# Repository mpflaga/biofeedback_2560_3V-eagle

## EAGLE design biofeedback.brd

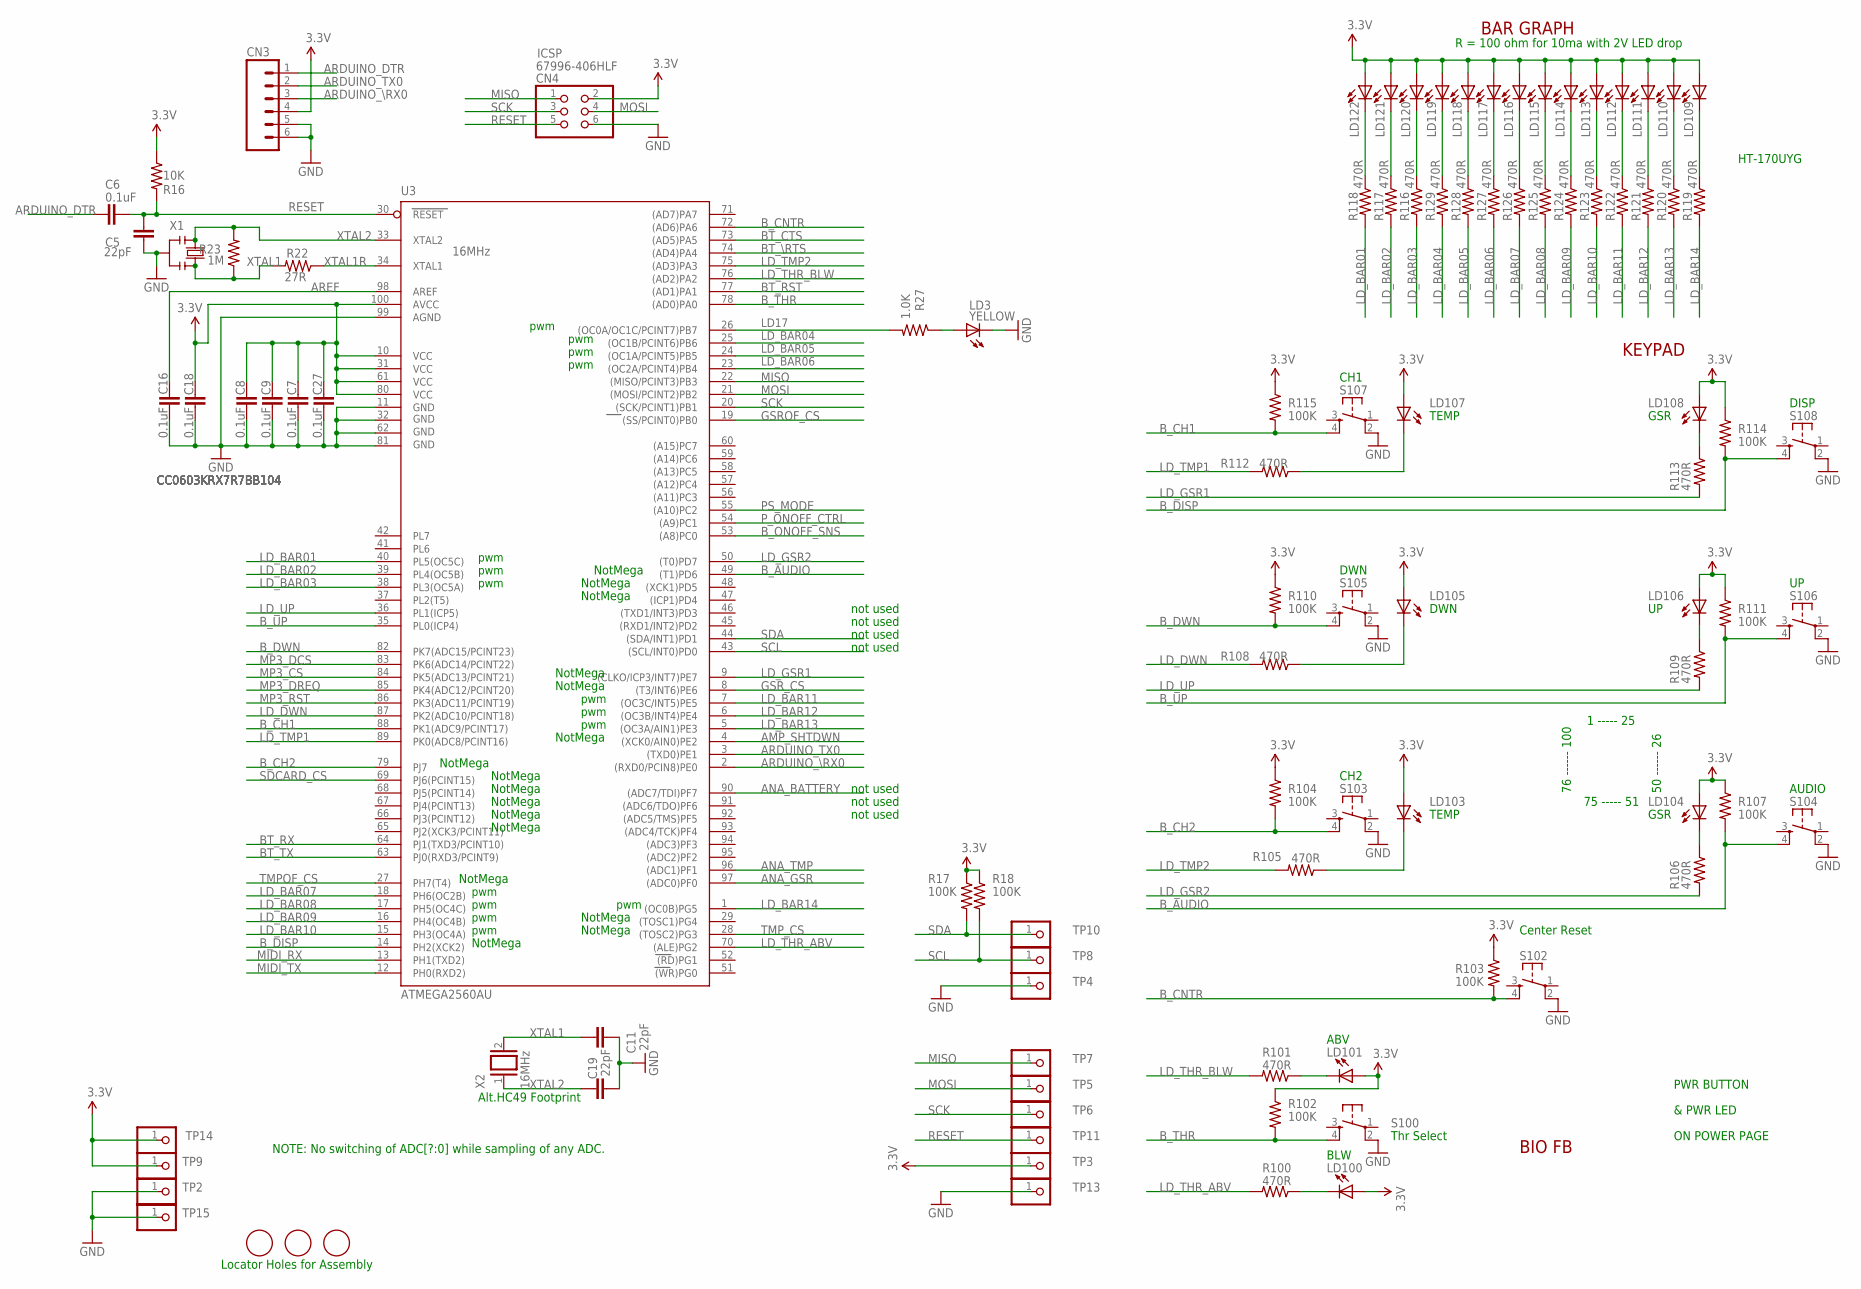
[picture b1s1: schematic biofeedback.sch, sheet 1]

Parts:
C5, C11, C19: 22pF; C0603; PARTNO GRM0335C1E220JD01D
C6, C7, C8, C9, C16, C18, C27: 0.1uF; C0603; PARTNO CC0603KRX7R7BB104
CN3: NSTUFF; 1X06; PARTNO 640456-6
CN4: ICSP; 2X03; PARTNO 67996-406HLF
LD3: YELLOW; CHIP-LED0805; PARTNO APT2012YC
LD100, LD101, LD103, LD104, LD105, LD106, LD107, LD108, LD109, LD110, LD111, LD112, LD113, LD114, LD115, LD116, LD117, LD118, LD119, LD120, LD121, LD122: GREEN; CHIP-LED0805; PARTNO LG R971-KN-1-0-20-R18
MN1, MN2, MN3: FIDUCIALMOUNT; FIDUCIA-MOUNT
R16: 10K; R0603; PARTNO RC0603JR-0710KL
R17, R18, R102, R103, R104, R107, R110, R111, R114, R115: 100K; R0603; PARTNO RC0603JR-07100KL
R22: 27R; R0603; PARTNO ERJ-3EKF27R0V
R23: 1M; R0603; PARTNO RC0603JR-071ML
R27: 1.0K; R0603; PARTNO RC0603JR-071KL
R100, R101, R105, R106, R108, R109, R112, R113, R116, R117, R118, R119, R120, R121, R122, R123, R124, R125, R126, R127, R128, R129: 470R; R0603; PARTNO RC0603JR-07470RL
S100, S102, S103, S104, S105, S106, S107, S108: SPST-NO; TACTILE_SWITCH_SMD_6MM_SQ; PARTNO TL3301PF160QG
TP2, TP3, TP4, TP5, TP6, TP7, TP8, TP9, TP10, TP11, TP13, TP14, TP15: NSTUFF; 1X01
U3: ATMEGA2560AU; TQFP100; PARTNO ATMEGA2560-16AU
X1: 16MHz; RESONATOR; PARTNO AWSCR-16.00CV-T
X2: 16MHz; QS; PARTNO ATS16B

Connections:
3.3V: C7.2, C8.2, C9.2, C18.2, C27.2, CN3.4, CN4.2, LD100.A, LD101.A, LD103.A, LD104.A, LD105.A, LD106.A, LD107.A, LD108.A, LD109.A, LD110.A, LD111.A, LD112.A, LD113.A, LD114.A, LD115.A, LD116.A, LD117.A, LD118.A, LD119.A, LD120.A, LD121.A, LD122.A, R16.1, R17.1, R18.1, R102.1, R103.1, R104.1, R107.1, R110.1, R111.1, R114.1, R115.1, TP3.1, TP9.1, TP14.1, U3.10 (VCC), U3.31 (VCC1), U3.61 (VCC2), U3.80 (VCC3), U3.100 (AVCC); also elsewhere on the board
AMP_SHTDWN: U3.4 ((XCK0/AIN0)PE2); also elsewhere on the board
ANA_BATTERY: U3.90 ((ADC7/TDI)PF7); also elsewhere on the board
ANA_GSR: U3.97 ((ADC0)PF0); also elsewhere on the board
ANA_TMP: U3.96 ((ADC1)PF1); also elsewhere on the board
ARDUINO_DTR: C6.1, CN3.1
ARDUINO_TX0: CN3.2, U3.3 ((TXD0)PE1)
ARDUINO_\RX0: CN3.3, U3.2 ((RXD0/PCIN8)PE0)
AREF: C16.2, U3.98 (AREF)
BT_CTS: U3.73 ((AD5)PA5); also elsewhere on the board
BT_RST: U3.77 ((AD1)PA1); also elsewhere on the board
BT_RX: U3.64 (PJ1(TXD3/PCINT10)); also elsewhere on the board
BT_TX: U3.63 (PJ0(RXD3/PCINT9)); also elsewhere on the board
BT_\RTS: U3.74 ((AD4)PA4); also elsewhere on the board
B_AUDIO: R107.2, S104.4, U3.49 ((T1)PD6)
B_CH1: R115.2, S107.4, U3.88 (PK1(ADC9/PCINT17))
B_CH2: R104.2, S103.4, U3.79 (PJ7)
B_CNTR: R103.2, S102.4, U3.72 ((AD6)PA6)
B_DISP: R114.2, S108.4, U3.14 (PH2(XCK2))
B_DWN: R110.2, S105.4, U3.82 (PK7(ADC15/PCINT23))
B_ONOFF_SNS: U3.53 ((A8)PC0); also elsewhere on the board
B_THR: R102.2, S100.4, U3.78 ((AD0)PA0)
B_UP: R111.2, S106.4, U3.35 (PL0(ICP4))
G2: LD107.C, R112.1
GND: C5.2, C7.1, C8.1, C9.1, C11.1, C16.1, C18.1, C19.1, C27.1, CN3.5, CN3.6, CN4.6, LD3.C, S100.2, S102.2, S103.2, S104.2, S105.2, S106.2, S107.2, S108.2, TP2.1, TP4.1, TP13.1, TP15.1, U3.11 (GND), U3.32 (GND1), U3.62 (GND2), U3.81 (GND3), U3.99 (AGND), X1.2; also elsewhere on the board
GSROF_CS: U3.19 ((SS/PCINT0)PB0); also elsewhere on the board
GSR_CS: U3.8 ((T3/INT6)PE6); also elsewhere on the board
LD17: R27.2, U3.26 ((OC0A/OC1C/PCINT7)PB7)
LD_BAR01: R118.2, U3.40 (PL5(OC5C))
LD_BAR02: R117.2, U3.39 (PL4(OC5B))
LD_BAR03: R116.2, U3.38 (PL3(OC5A))
LD_BAR04: R129.2, U3.25 ((OC1B/PCINT6)PB6)
LD_BAR05: R128.2, U3.24 ((OC1A/PCINT5)PB5)
LD_BAR06: R127.2, U3.23 ((OC2A/PCINT4)PB4)
LD_BAR07: R126.2, U3.18 (PH6(OC2B))
LD_BAR08: R125.2, U3.17 (PH5(OC4C))
LD_BAR09: R124.2, U3.16 (PH4(OC4B))
LD_BAR10: R123.2, U3.15 (PH3(OC4A))
LD_BAR11: R122.2, U3.7 ((OC3C/INT5)PE5)
LD_BAR12: R121.2, U3.6 ((OC3B/INT4)PE4)
LD_BAR13: R120.2, U3.5 ((OC3A/AIN1)PE3)
LD_BAR14: R119.2, U3.1 ((OC0B)PG5)
LD_DWN: R108.2, U3.87 (PK2(ADC10/PCINT18))
LD_GSR1: R113.2, U3.9 ((CLKO/ICP3/INT7)PE7)
LD_GSR2: R106.2, U3.50 ((T0)PD7)
LD_THR_ABV: R100.2, U3.70 ((ALE)PG2)
LD_THR_BLW: R101.2, U3.76 ((AD2)PA2)
LD_TMP1: R112.2, U3.89 (PK0(ADC8/PCINT16))
LD_TMP2: R105.2, U3.75 ((AD3)PA3)
LD_UP: R109.2, U3.36 (PL1(ICP5))
MIDI_RX: U3.13 (PH1(TXD2)); also elsewhere on the board
MIDI_TX: U3.12 (PH0(RXD2)); also elsewhere on the board
MISO: CN4.1, TP7.1, U3.22 ((MISO/PCINT3)PB3); also elsewhere on the board
MOSI: CN4.4, TP5.1, U3.21 ((MOSI/PCINT2)PB2); also elsewhere on the board
MP3_CS: U3.84 (PK5(ADC13/PCINT21)); also elsewhere on the board
MP3_DCS: U3.83 (PK6(ADC14/PCINT22)); also elsewhere on the board
MP3_DREQ: U3.85 (PK4(ADC12/PCINT20)); also elsewhere on the board
MP3_RST: U3.86 (PK3(ADC11/PCINT19)); also elsewhere on the board
unnamed: LD105.C, R108.1
unnamed: LD106.C, R109.1
unnamed: LD122.C, R118.1
unnamed: LD121.C, R117.1
unnamed: LD120.C, R116.1
unnamed: LD119.C, R129.1
unnamed: LD118.C, R128.1
unnamed: LD117.C, R127.1
unnamed: LD116.C, R126.1
unnamed: LD115.C, R125.1
unnamed: LD114.C, R124.1
unnamed: LD113.C, R123.1
unnamed: LD112.C, R122.1
unnamed: LD111.C, R121.1
unnamed: LD110.C, R120.1
unnamed: LD109.C, R119.1
unnamed: LD103.C, R105.1
unnamed: LD104.C, R106.1
unnamed: LD101.C, R101.1
unnamed: LD100.C, R100.1
unnamed: LD108.C, R113.1
unnamed: LD3.A, R27.1
PS_MODE: U3.55 ((A10)PC2); also elsewhere on the board
P_ONOFF_CTRL: U3.54 ((A9)PC1); also elsewhere on the board
RESET: C5.1, C6.2, CN4.5, R16.2, TP11.1, U3.30 (RESET)
SCK: CN4.3, TP6.1, U3.20 ((SCK/PCINT1)PB1); also elsewhere on the board
SCL: R18.2, TP8.1, U3.43 ((SCL/INT0)PD0)
SDA: R17.2, TP10.1, U3.44 ((SDA/INT1)PD1)
SDCARD_CS: U3.69 (PJ6(PCINT15)); also elsewhere on the board
TMPOF_CS: U3.27 (PH7(T4)); also elsewhere on the board
TMP_CS: U3.28 ((TOSC2)PG3); also elsewhere on the board
XTAL1: C11.2, R22.2, R23.1, X1.3, X2.2
XTAL1R: R22.1, U3.34 (XTAL1)
XTAL2: C19.2, R23.2, U3.33 (XTAL2), X1.1, X2.1

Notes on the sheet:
Alt.HC49 Footprint
BIO FB
pwm
NOTE: No switching of ADC[?:0] while sampling of any ADC.
BAR GRAPH
CH1
ABV
BLW
DISP
DWN
Thr Select
Center Reset
KEYPAD
CH2
AUDIO
TEMP
PWR BUTTON
& PWR LED
ON POWER PAGE
Locator Holes for Assembly
not used
NotMega
GSR
R = 100 ohm for 10ma with 2V LED drop
HT-170UYG
1 ----- 25
75 ----- 51
50 ------ 26
76 ------ 100

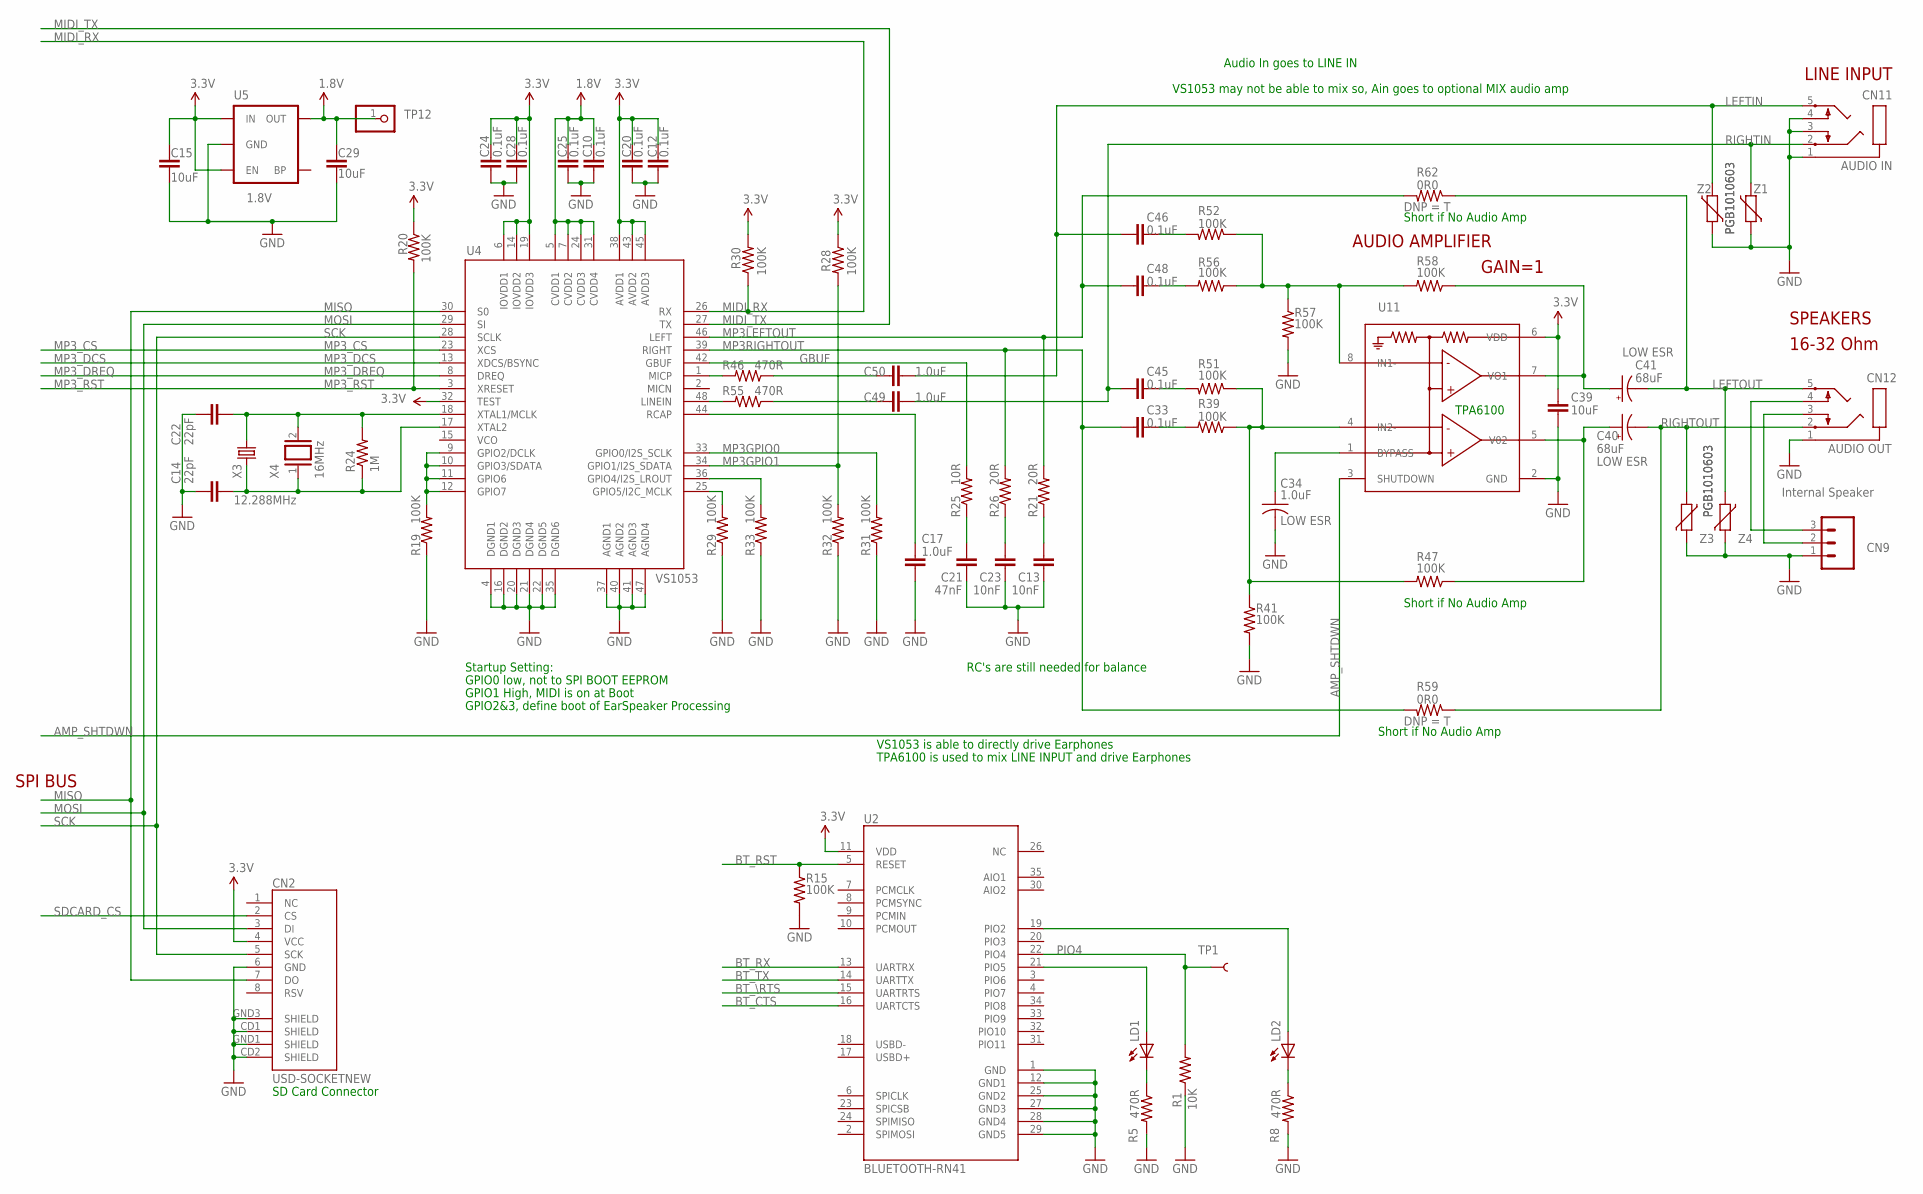
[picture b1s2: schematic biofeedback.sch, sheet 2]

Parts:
C10, C12, C20, C24, C25, C28, C33, C45, C46, C48: 0.1uF; C0603; PARTNO CC0603KRX7R7BB104
C13, C23: 10nF; C0603; PARTNO CC0603KRX7R9BB103
C14, C22: 22pF; C0603; PARTNO GRM0335C1E220JD01D
C15, C29, C39: 10uF; C0603; PARTNO C1608X5R1A106M
C17, C49, C50: 1.0uF; C0603; PARTNO GRM188R61A105KA61D
C21: 47nF; C0603; PARTNO CC0603KRX7R8BB473
C34: 1.0uF; C0805; PARTNO ECP-U1C104MA5
C40, C41: 68uF; CT7343; PARTNO T491C686K006AT
CN2: USD-SOCKETNEW; MICRO-SD-SOCKET-PP; PARTNO 101-00581-59
CN9: Internal Speaker; 1X03; PARTNO 640454-3
CN11: AUDIO IN; STX3100; PARTNO SJ1-3555NG-BE
CN12: AUDIO OUT; STX3100; PARTNO SJ1-3555NG-GR
LD1, LD2: GREEN; CHIP-LED0805; PARTNO LG R971-KN-1-0-20-R18
R1: 10K; R0603; PARTNO RC0603JR-0710KL
R5, R8, R46, R55: 470R; R0603; PARTNO RC0603JR-07470RL
R15, R19, R20, R28, R29, R30, R31, R32, R33, R39, R41, R47, R51, R52, R56, R57, R58: 100K; R0603; PARTNO RC0603JR-07100KL
R21, R26: 20R; R0603; PARTNO RC0603JR-0720RL
R24: 1M; R0603; PARTNO RC0603JR-071ML
R25: 10R; R0603; PARTNO RC0603JR-0710RL
R59, R62: 0R0; R0603; PARTNO RC0603JR-070RL
TP1: TEST-POINT3X5; PAD.03X.05
TP12: NSTUFF; 1X01
U2: BLUETOOTH-RN41; RN41; PARTNO RN-42
U4: VS1053; LQFP-48; PARTNO VS1053B-L
U5: 1.8V; SC70; PARTNO MIC5365-1.8YC5
U11: TPA6100; SO-08; PARTNO TPA6100A2DR
X3: 12.288MHz; CRYSTAL-SMD-5X3; PARTNO ATS122B
X4: 16MHz; QS_COMBO; PARTNO ATS16B
Z1, Z2, Z3, Z4: PGB1010603; CT/CN0603; PARTNO PGB1010603MR

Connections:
1.8V: C10.1, C25.1, C29.1, TP12.1, U4.5 (CVDD1), U4.7 (CVDD2), U4.24 (CVDD3), U4.31 (CVDD4), U5.5 (OUT)
3.3V: C12.1, C15.1, C20.1, C24.1, C28.1, C39.1, CN2.4 (VCC), R20.1, R28.1, R30.2, U2.11 (VDD), U4.6 (IOVDD1), U4.14 (IOVDD2), U4.19 (IOVDD3), U4.32 (TEST), U4.38 (AVDD1), U4.43 (AVDD2), U4.45 (AVDD3), U5.1 (IN), U5.3 (EN), U11.6 (VDD); also elsewhere on the board
AMP_SHTDWN: U11.3 (SHUTDOWN); also elsewhere on the board
BT_CTS: U2.16 (UARTCTS); also elsewhere on the board
BT_RST: R15.1, U2.5 (RESET); also elsewhere on the board
BT_RX: U2.13 (UARTRX); also elsewhere on the board
BT_TX: U2.14 (UARTTX); also elsewhere on the board
BT_\RTS: U2.15 (UARTRTS); also elsewhere on the board
D1: LD1.C, R5.1
D2: LD2.C, R8.1
GBUF: R25.2, U4.42 (GBUF)
GND: C10.2, C12.2, C13.2, C14.1, C15.2, C17.1, C20.2, C21.2, C22.1, C23.2, C24.2, C25.2, C28.2, C29.2, C34.2, C39.2, CN2.6 (GND), CN2.CD1 (SHIELD), CN2.CD2 (SHIELD), CN2.GND1 (SHIELD), CN2.GND3 (SHIELD), CN9.1, CN11.1, CN11.3, CN11.4, CN12.1, R1.1, R5.2, R8.2, R15.2, R19.1, R29.1, R31.1, R32.1, R33.1, R41.2, R57.2, U2.1 (GND), U2.12 (GND1), U2.25 (GND2), U2.27 (GND3), U2.28 (GND4), U2.29 (GND5), U4.4 (DGND1), U4.16 (DGND2), U4.20 (DGND3), U4.21 (DGND4), U4.22 (DGND5), U4.35 (DGND6), U4.37 (AGND1), U4.40 (AGND2), U4.41 (AGND3), U4.47 (AGND4), U5.2 (GND), U11.2 (GND), Z1.2, Z2.2, Z3.2, Z4.2; also elsewhere on the board
LEFTIN: C46.1, C50.1, CN11.5, Z2.1
LEFTOUT: C41.-, CN12.5, R62.1, Z4.1
LEFTOUTSPKR: CN9.3, CN12.4
MIDI_RX: R30.1, U4.26 (RX); also elsewhere on the board
MIDI_TX: U4.27 (TX); also elsewhere on the board
MISO: CN2.7 (DO), U4.30 (S0); also elsewhere on the board
MOSI: CN2.3 (DI), U4.29 (SI); also elsewhere on the board
MP3GPIO0: R31.2, U4.33 (GPIO0/I2S_SCLK)
MP3GPIO1: R28.2, R32.2, U4.34 (GPIO1/I2S_SDATA)
MP3LEFTOUT: C48.1, R21.2, R62.2, U4.46 (LEFT)
MP3LINEINLEFT: R46.2, U4.1 (MICP)
MP3LINEINRIGHT: R55.2, U4.48 (LINEIN)
MP3RCAP: C17.2, U4.44 (RCAP)
MP3RIGHTOUT: C33.1, R26.2, R59.2, U4.39 (RIGHT)
MP3_CS: U4.23 (XCS); also elsewhere on the board
MP3_DCS: U4.13 (XDCS/BSYNC); also elsewhere on the board
MP3_DREQ: U4.8 (DREQ); also elsewhere on the board
MP3_RST: R20.2, U4.3 (XRESET); also elsewhere on the board
unnamed: R52.1, R56.1, R57.1, R58.2, U11.8 (IN1-)
unnamed: C21.1, R25.1
unnamed: C13.1, R21.1
unnamed: C46.2, R52.2
unnamed: C23.1, R26.1
unnamed: R39.1, R41.1, R47.2, R51.1, U11.4 (IN2-)
unnamed: C14.2, R24.1, U4.17 (XTAL2), X3.1, X4.1
unnamed: C45.2, R51.2
unnamed: C41.+, R58.1, U11.7 (VO1)
unnamed: C40.+, R47.1, U11.5 (V02)
unnamed: C48.2, R56.2
unnamed: C33.2, R39.2
unnamed: C34.1, U11.1 (BYPASS)
unnamed: LD1.A, U2.21 (PIO5)
unnamed: R19.2, U4.9 (GPIO2/DCLK), U4.10 (GPIO3/SDATA), U4.11 (GPIO6), U4.12 (GPIO7)
unnamed: LD2.A, U2.19 (PIO2)
unnamed: R33.2, U4.36 (GPIO4/I2S_LROUT)
unnamed: R29.2, U4.25 (GPIO5/I2C_MCLK)
unnamed: C50.2, R46.1
unnamed: C49.2, R55.1
unnamed: C22.2, R24.2, U4.18 (XTAL1/MCLK), X3.3 (2), X4.2
PIO4: R1.2, TP1.P$1, U2.22 (PIO4)
RIGHTIN: C45.1, C49.1, CN11.2, Z1.1
RIGHTOUT: C40.-, CN12.2, R59.1, Z3.1
RIGHTOUTSPKR: CN9.2, CN12.3
SCK: CN2.5 (SCK), U4.28 (SCLK); also elsewhere on the board
SDCARD_CS: CN2.2 (CS); also elsewhere on the board

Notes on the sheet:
GPIO0 low, not to SPI BOOT EEPROM
GPIO1 High, MIDI is on at Boot
GPIO2&3, define boot of EarSpeaker Processing
Startup Setting:
SD Card Connector
SPI BUS
AUDIO AMPLIFIER
LINE INPUT
16-32 Ohm
SPEAKERS
VS1053 is able to directly drive Earphones
TPA6100 is used to mix LINE INPUT and drive Earphones
RC's are still needed for balance
TPA6100
Short if No Audio Amp
GAIN=1
Audio In goes to LINE IN
VS1053 may not be able to mix so, Ain goes to optional MIX audio amp

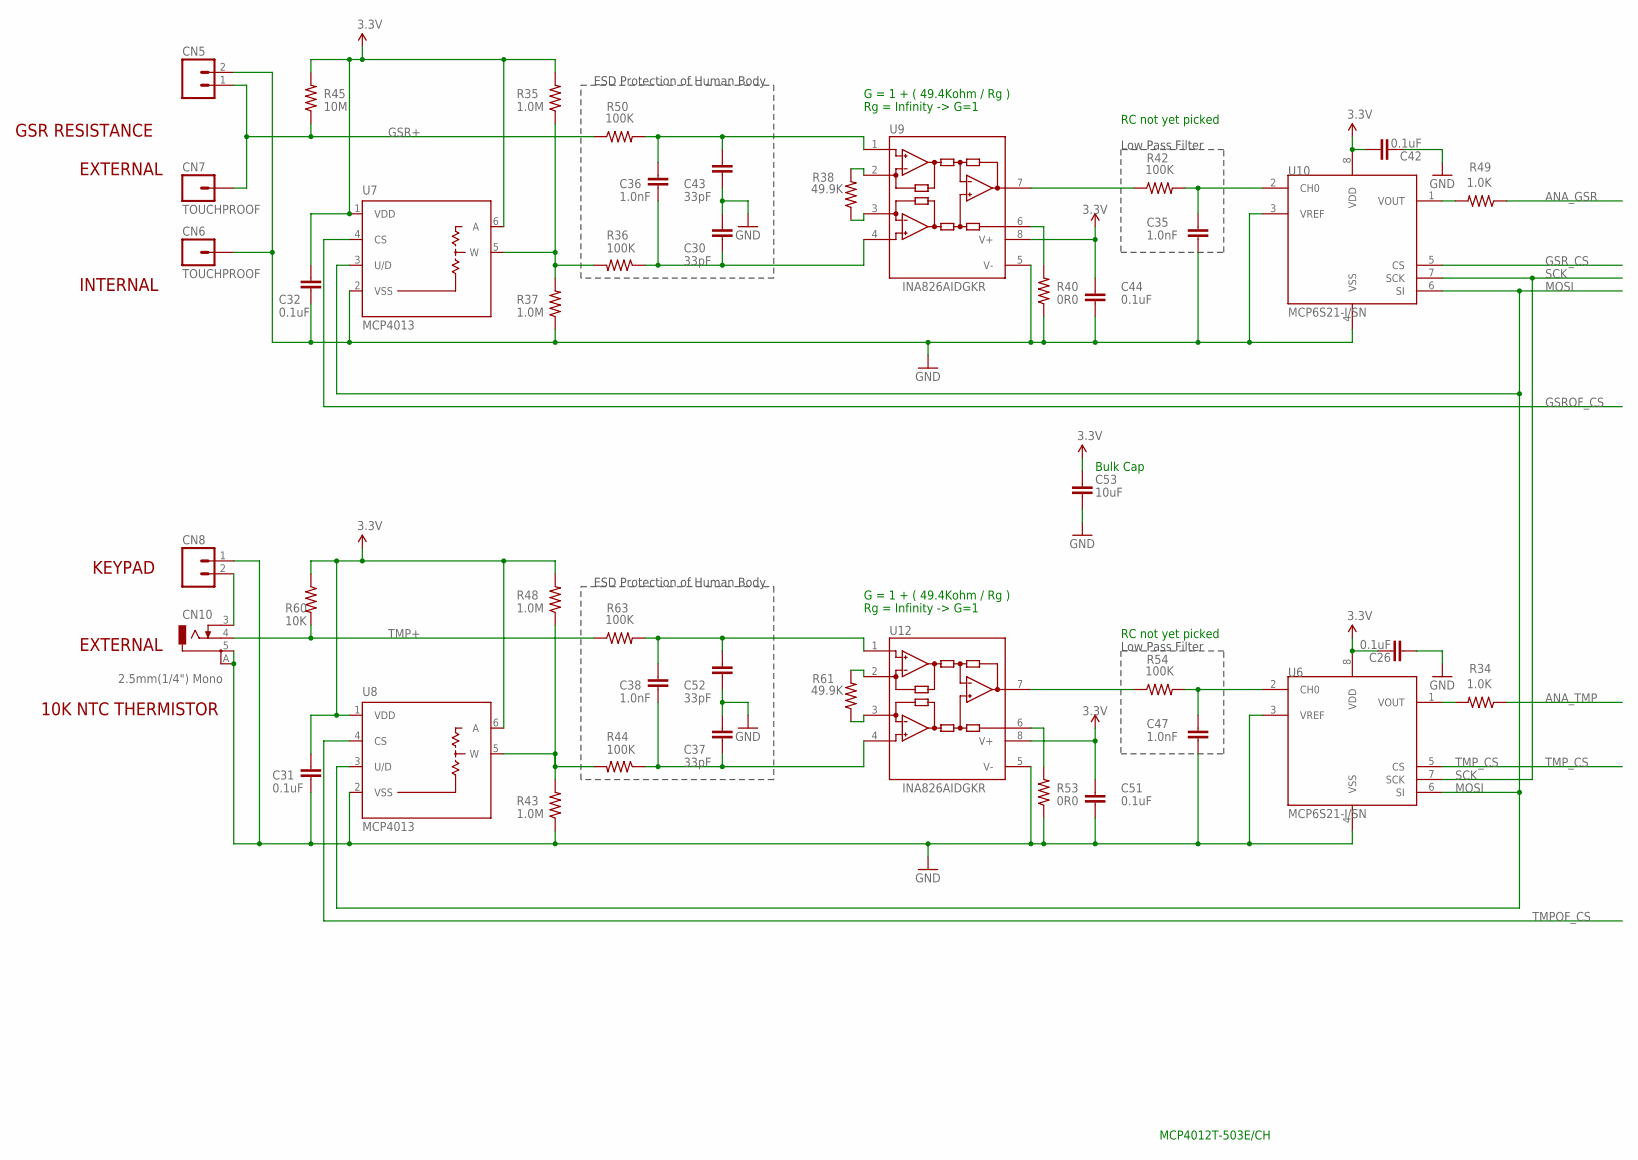
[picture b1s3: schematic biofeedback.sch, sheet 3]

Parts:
C26, C31, C32, C42, C44, C51: 0.1uF; C0603; PARTNO CC0603KRX7R7BB104
C30, C37, C43, C52: 33pF; C0603; PARTNO GRM0335C1E330JD01D
C35, C36, C38, C47: 1.0nF; C0603; PARTNO CC0603KRX7R9BB102
C53: 10uF; C0603; PARTNO C1608X5R1A106M
CN5, CN8: CONN HEADER PH TOP 2POS 2MM; 1X02; PARTNO B2B-PH-K-S(LF)(SN)
CN6, CN7: TOUCHPROOF; TOUCHPROOF1.1MM; PARTNO 36619
CN10: 2.5mm(1/4") Mono; STEREOJACK2.5MM_SMD; PARTNO MDSMT2ARATRX
R34, R49: 1.0K; R0603; PARTNO RC0603JR-071KL
R35, R37, R43, R48: 1.0M; R0603; PARTNO RC0603JR-071ML
R36, R42, R44, R50, R54, R63: 100K; R0603; PARTNO RC0603JR-07100KL
R38, R61: 49.9K; R0603; PARTNO ERJ-3EKF4992V
R40, R53: 0R0; R0603; PARTNO RC0603JR-070RL
R45: 10M; R0603; PARTNO RC0603JR-0710ML
R60: 10K; R0603; PARTNO RC0603JR-0710KL
U6, U10: MCP6S21-I/SN; SO-08; PARTNO MCP6S21-I/SN
U7, U8: MCP4013; SOT-23-6; PARTNO MCP4013T-103E/CH
U9, U12: INA826; MSOP-8; PARTNO INA826AIDGKR

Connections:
3.3V: C26.1, C31.1, C32.1, C42.1, C44.1, C51.1, C53.1, R35.2, R45.2, R48.2, R60.1, U6.8 (VDD), U7.1 (VDD), U7.6 (A), U8.1 (VDD), U8.6 (A), U9.8 (V+), U10.8 (VDD), U12.8 (V+); also elsewhere on the board
ANA_GSR: R49.1; also elsewhere on the board
ANA_TMP: R34.1; also elsewhere on the board
GND: C26.2, C30.1, C31.2, C32.2, C35.2, C37.1, C42.2, C43.2, C44.2, C47.2, C51.2, C52.2, C53.2, CN5.2, CN6.P$1, CN8.1, CN10.5, CN10.A, R37.1, R40.1, R43.1, R53.1, U6.3 (VREF), U6.4 (VSS), U7.2 (VSS), U8.2 (VSS), U9.5 (V-), U10.3 (VREF), U10.4 (VSS), U12.5 (V-); also elsewhere on the board
GSR+: CN5.1, CN7.P$1, R45.1, R50.1
GSROF_CS: U7.4 (CS); also elsewhere on the board
GSR_CS: U10.5 (CS); also elsewhere on the board
MOSI: U6.6 (SI), U7.3 (U/D), U8.3 (U/D), U10.6 (SI); also elsewhere on the board
unnamed: R38.2, U9.2 (RG)
unnamed: R38.1, U9.3 (RG)
unnamed: C30.2, C36.2, R36.1, U9.4 (+IN)
unnamed: C36.1, C43.1, R50.2, U9.1 (-IN)
unnamed: R42.1, U9.7 (OUT)
unnamed: C35.1, R42.2, U10.2 (CH0)
unnamed: R61.2, U12.2 (RG)
unnamed: R61.1, U12.3 (RG)
unnamed: C38.1, C52.1, R63.2, U12.1 (-IN)
unnamed: C37.2, C38.2, R44.1, U12.4 (+IN)
unnamed: R54.1, U12.7 (OUT)
unnamed: C47.1, R54.2, U6.2 (CH0)
unnamed: R53.2, U12.6 (REF)
unnamed: R34.2, U6.1 (VOUT)
unnamed: R43.2, R44.2, R48.1, U8.5 (W)
unnamed: CN8.2, CN10.3
unnamed: R35.1, R36.2, R37.2, U7.5 (W)
unnamed: R49.2, U10.1 (VOUT)
unnamed: R40.2, U9.6 (REF)
SCK: U6.7 (SCK), U10.7 (SCK); also elsewhere on the board
TMP+: CN10.4, R60.2, R63.1
TMPOF_CS: U8.4 (CS); also elsewhere on the board
TMP_CS: U6.5 (CS); also elsewhere on the board

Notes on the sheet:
EXTERNAL
10K NTC THERMISTOR
GSR RESISTANCE
INTERNAL
KEYPAD
MCP4012T-503E/CH
ESD Protection of Human Body
Low Pass Filter
G = 1 + ( 49.4Kohm / Rg )
RC not yet picked
Rg = Infinity -> G=1
Bulk Cap

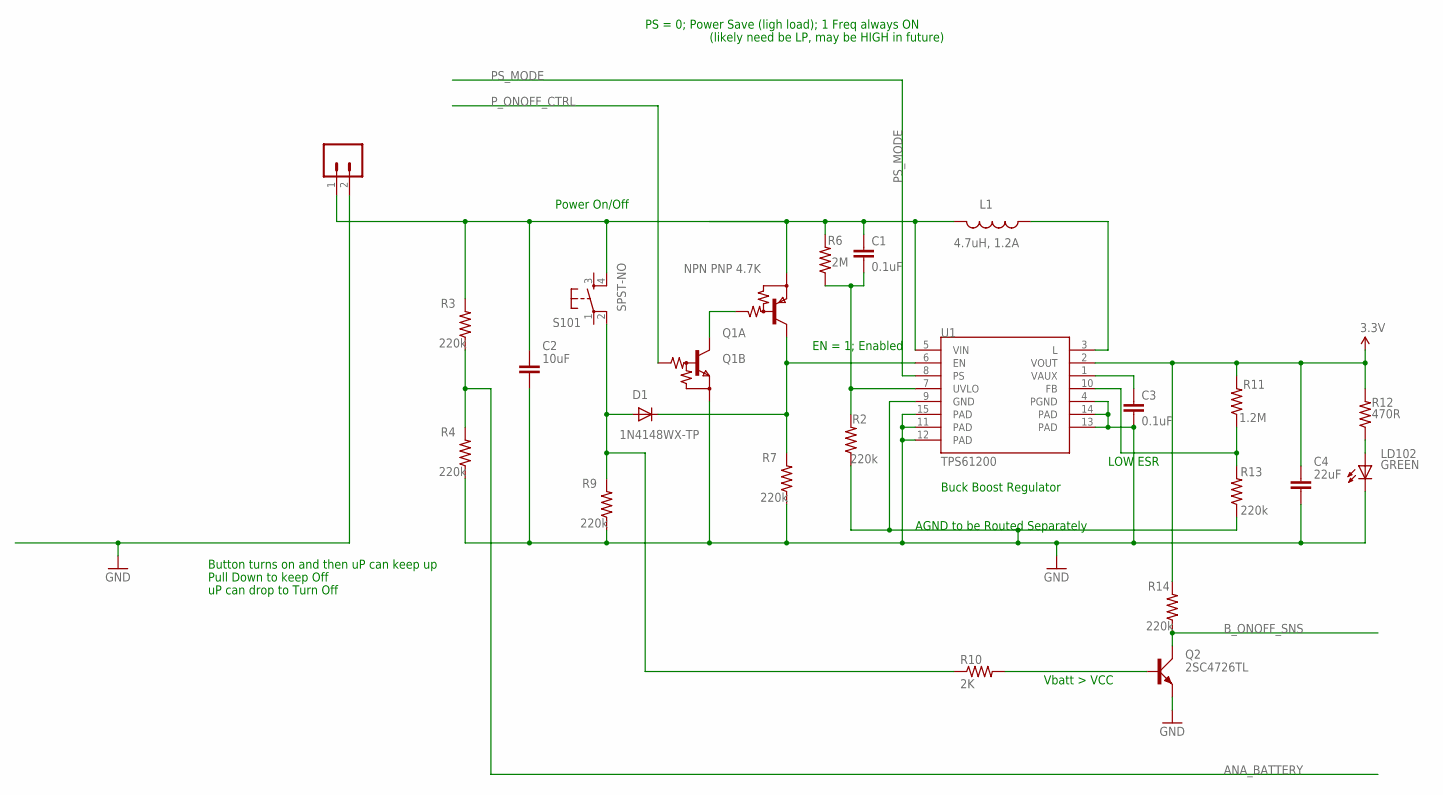
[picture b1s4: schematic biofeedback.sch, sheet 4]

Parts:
C1, C3: 0.1uF; C0603; PARTNO CC0603KRX7R7BB104
C2: 10uF; C0603; PARTNO C1608X5R1A106M
C4: 22uF; C0603; PARTNO 250R14W224KV4T
CN1: CONN HEADER PH TOP 2POS 2MM; 1X02; PARTNO B2B-PH-K-S(LF)(SN)
D1: 1N4148WX-TP; SOD323-R; PARTNO 1N4148WX-TP
L1: 4.7uH, 1.2A; CDRH2D09; PARTNO CDRH2D09NP-4R7MC
LD102: GREEN; CHIP-LED0805; PARTNO LG R971-KN-1-0-20-R18
Q1: NPN PNP 4.7K; SOT-23-6; PARTNO DMG264060R
Q2: 2SC4726TL; EMT3; PARTNO MMBT3904TT1G
R2, R3, R4, R7, R9, R13, R14: 220k; R0603; PARTNO RC0603JR-07220KL
R6: 2M; R0603; PARTNO RC0603JR-072ML
R10: 2K; R0603; PARTNO RC0603JR-072KL
R11: 1.2M; R0603; PARTNO CRCW04021M20FKED
R12: 470R; R0603; PARTNO RC0603JR-07470RL
S101: SPST-NO; TACTILE_SWITCH_SMD_6MM_SQ; PARTNO TL3301PF160QG
U1: TPS61200; QFN-10_PAD; PARTNO TPS61200DRCT

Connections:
3.3V: C4.1, R11.2, R12.2, R14.2, U1.2 (VOUT); also elsewhere on the board
ANA_BATTERY: R3.1, R4.2; also elsewhere on the board
B_ONOFF_SNS: Q2.C, R14.1; also elsewhere on the board
FB: R11.1, R13.2, U1.10 (FB)
GND: C2.2, C3.2, C4.2, CN1.2, LD102.C, Q1.1 (E), Q2.E, R2.1, R4.1, R7.1, R9.1, R13.1, U1.4 (PGND), U1.9 (GND), U1.11 (PAD), U1.12 (PAD), U1.13 (PAD), U1.14 (PAD), U1.15 (PAD); also elsewhere on the board
unnamed: LD102.A, R12.1
unnamed: Q1.5 (B), Q1.6 (C)
unnamed: L1.P$1 (1), U1.3 (L)
unnamed: C3.1, U1.1 (VAUX)
unnamed: D1.C, Q1.3 (C), R7.2, U1.6 (EN)
unnamed: D1.A, R9.2, R10.1, S101.2
unnamed: Q2.B, R10.2
PS_MODE: U1.8 (PS); also elsewhere on the board
P_ONOFF_CTRL: Q1.2 (B); also elsewhere on the board
UVLO: C1.2, R2.2, R6.1, U1.7 (UVLO)
VIN: C1.1, C2.1, CN1.1, L1.P$2 (2), Q1.4 (E), R3.2, R6.2, S101.4, U1.5 (VIN)

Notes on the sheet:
Buck Boost Regulator
AGND to be Routed Separately
Power On/Off
PS = 0; Power Save (ligh load); 1 Freq always ON
EN = 1; Enabled
Pull Down to keep Off
Button turns on and then uP can keep up
(likely need be LP, may be HIGH in future)
uP can drop to Turn Off
Vbatt > VCC
LOW ESR

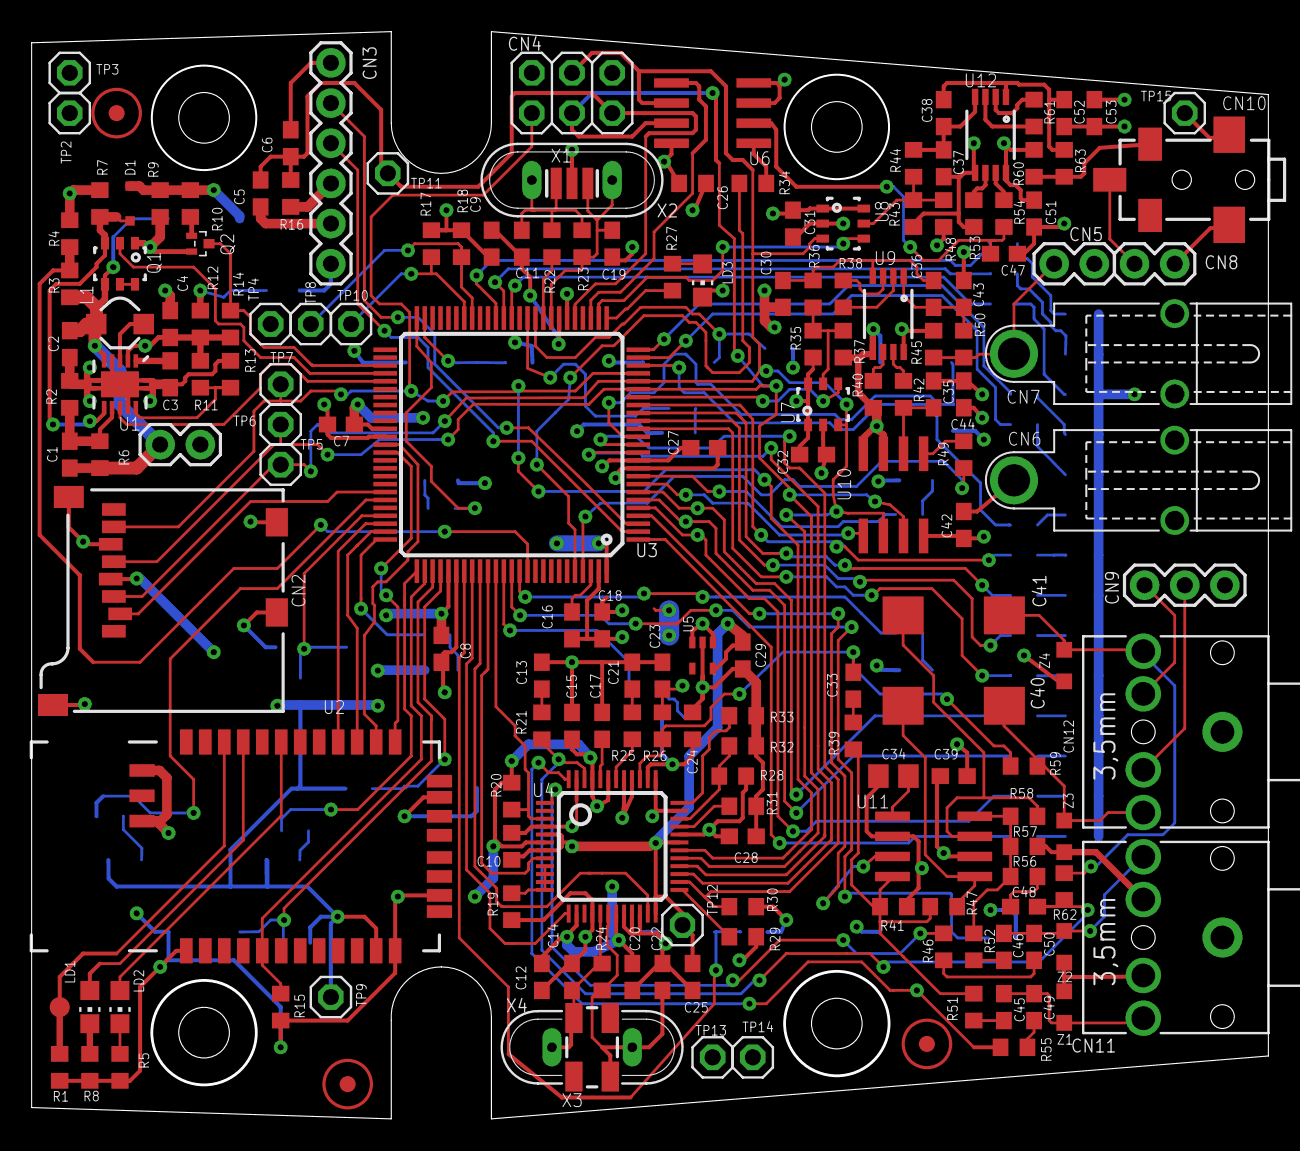
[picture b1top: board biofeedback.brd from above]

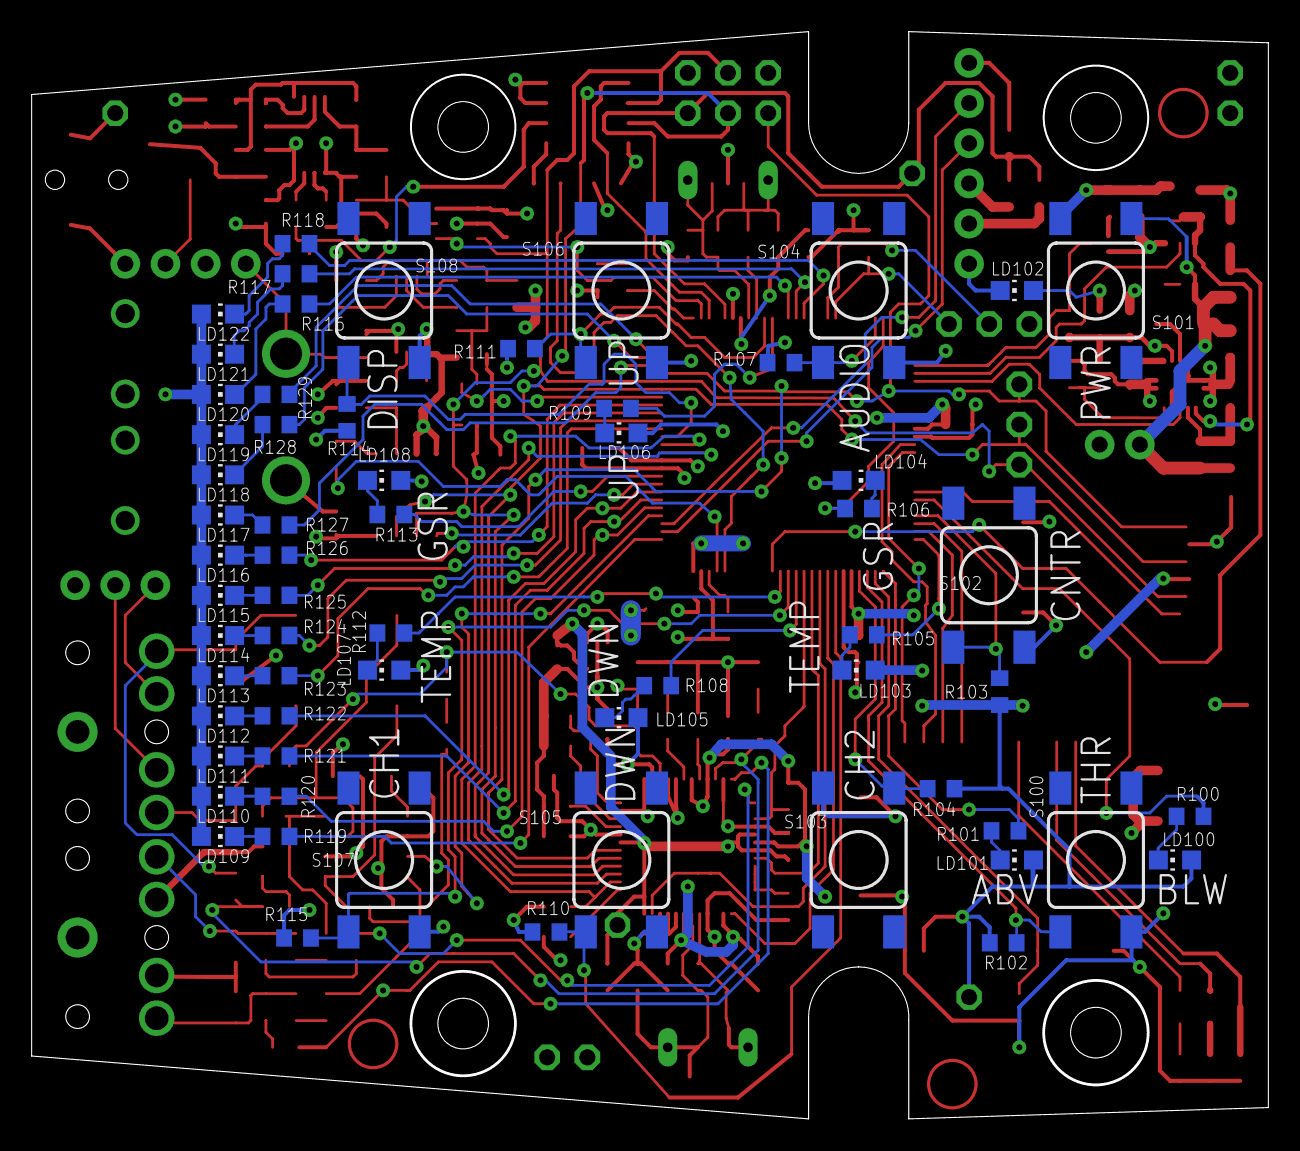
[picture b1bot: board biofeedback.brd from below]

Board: 4 copper layers, 78.0 x 68.6 mm, 235 parts (62 on the bottom side), 162 nets.

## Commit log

2012-07-17 Initial Commit from what was built
2013-08-01 renamed eagle files to match boards.txt biofeedback-mega:biofeedback_2560_3V
2013-08-06 Added PDF of schematic
